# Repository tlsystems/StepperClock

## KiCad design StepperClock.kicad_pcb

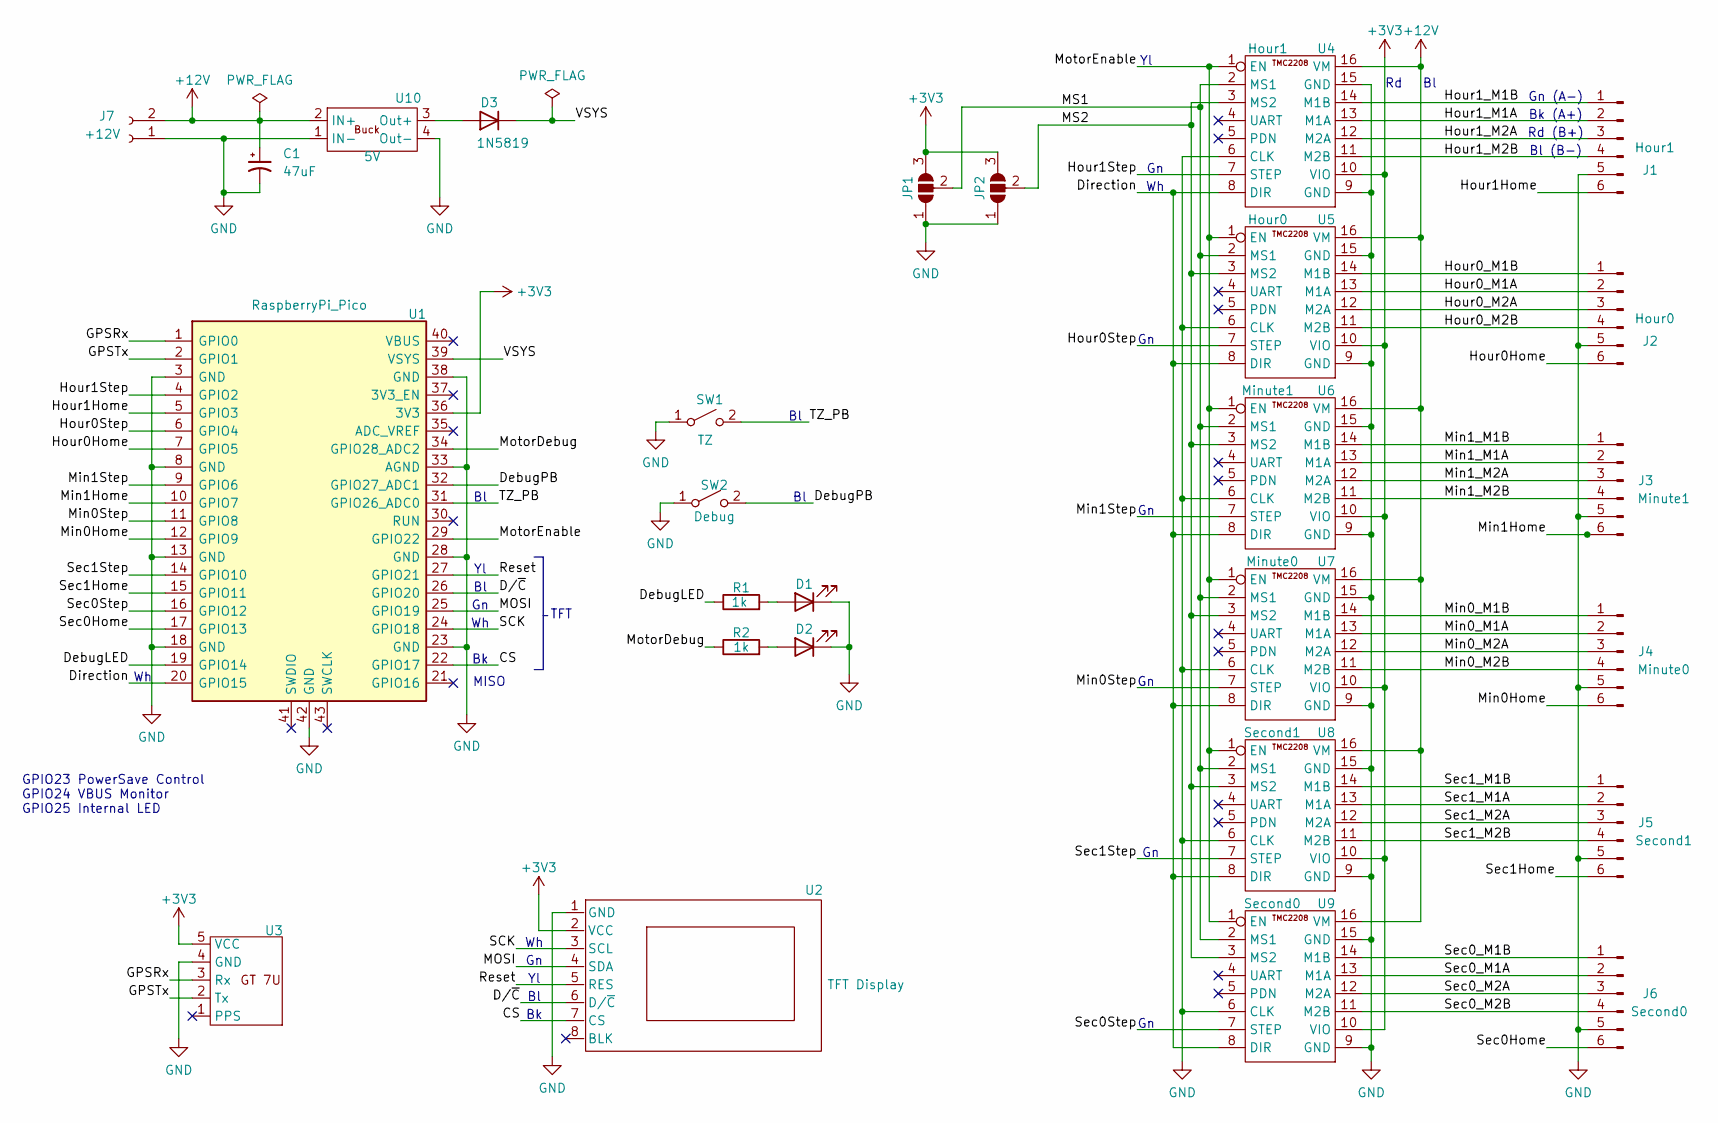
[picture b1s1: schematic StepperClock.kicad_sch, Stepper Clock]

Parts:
C1: 47uF; CP_Radial_D8.0mm_P2.50mm
D1, D2: LED; D_0805_2012Metric_Pad1.15x1.40mm_HandSolder
D3: 1N5819; D_DO-41_SOD81_P7.62mm_Horizontal
J1: Hour1; JST_PH_B6B-PH-K_1x06_P2.00mm_Vertical
J2: Hour0; JST_PH_B6B-PH-K_1x06_P2.00mm_Vertical
J3: Minute1; JST_PH_B6B-PH-K_1x06_P2.00mm_Vertical
J4: Minute0; JST_PH_B6B-PH-K_1x06_P2.00mm_Vertical
J5: Second1; JST_PH_B6B-PH-K_1x06_P2.00mm_Vertical
J6: Second0; JST_PH_B6B-PH-K_1x06_P2.00mm_Vertical
J7: +12V; PinHeader_1x02_P2.54mm_Vertical
JP1, JP2: SolderJumper-3_P2.0mm_Open_TrianglePad1.0x1.5mm
R1, R2: 1k; R_0805_2012Metric_Pad1.20x1.40mm_HandSolder
SW1: TZ; SW_PUSH-12mm
SW2: Debug; SW_PUSH-12mm
U1: RaspberryPi_Pico; RaspberryPi_Pico_Common_THT
U2: TFT Display; TFT_Display_.94in
U3: GT-U7 GPS
U4: Hour1; TMC2208_Breakout
U5: Hour0; TMC2208_Breakout
U6: Minute1; TMC2208_Breakout
U7: Minute0; TMC2208_Breakout
U8: Second1; TMC2208_Breakout
U9: Second0; TMC2208_Breakout
U10: 5V; 5V Buck Converter

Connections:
+3V3: JP1.3 (B), JP2.3 (B), U1.36 (3V3), U2.2 (VCC), U3.5 (VCC), U4.10 (VIO), U5.10 (VIO), U6.10 (VIO), U7.10 (VIO), U8.10 (VIO), U9.10 (VIO)
+12V: C1.1, J7.2, U4.16 (VM), U5.16 (VM), U6.16 (VM), U7.16 (VM), U8.16 (VM), U9.16 (VM), U10.2 (IN+)
/CS: U1.22 (GPIO17), U2.7 (CS)
/DebugLED: R1.1, U1.19 (GPIO14)
/DebugPB: SW2.2 (B), U1.32 (GPIO27_ADC1)
/Direction: U1.20 (GPIO15), U4.8 (DIR), U5.8 (DIR), U6.8 (DIR), U7.8 (DIR), U8.8 (DIR), U9.8 (DIR)
/D/~C: U1.26 (GPIO20), U2.6 (D/~C)
/GPSRx: U1.1 (GPIO0), U3.3 (Rx)
/GPSTx: U1.2 (GPIO1), U3.2 (Tx)
/Hour0Home: J2.6, U1.7 (GPIO5)
/Hour0Step: U1.6 (GPIO4), U5.7 (STEP)
/Hour0_M1A: J2.2, U5.13 (M1A)
/Hour0_M1B: J2.1, U5.14 (M1B)
/Hour0_M2A: J2.3, U5.12 (M2A)
/Hour0_M2B: J2.4, U5.11 (M2B)
/Hour1Home: J1.6, U1.5 (GPIO3)
/Hour1Step: U1.4 (GPIO2), U4.7 (STEP)
/Hour1_M1A: J1.2, U4.13 (M1A)
/Hour1_M1B: J1.1, U4.14 (M1B)
/Hour1_M2A: J1.3, U4.12 (M2A)
/Hour1_M2B: J1.4, U4.11 (M2B)
/MOSI: U1.25 (GPIO19), U2.4 (SDA)
/MS1: JP1.2 (C), U4.2 (MS1), U5.2 (MS1), U6.2 (MS1), U7.2 (MS1), U8.2 (MS1), U9.2 (MS1)
/MS2: JP2.2 (C), U4.3 (MS2), U5.3 (MS2), U6.3 (MS2), U7.3 (MS2), U8.3 (MS2), U9.3 (MS2)
/Min0Home: J4.6, U1.12 (GPIO9)
/Min0Step: U1.11 (GPIO8), U7.7 (STEP)
/Min0_M1A: J4.2, U7.13 (M1A)
/Min0_M1B: J4.1, U7.14 (M1B)
/Min0_M2A: J4.3, U7.12 (M2A)
/Min0_M2B: J4.4, U7.11 (M2B)
/Min1Home: J3.6, U1.10 (GPIO7)
/Min1Step: U1.9 (GPIO6), U6.7 (STEP)
/Min1_M1A: J3.2, U6.13 (M1A)
/Min1_M1B: J3.1, U6.14 (M1B)
/Min1_M2A: J3.3, U6.12 (M2A)
/Min1_M2B: J3.4, U6.11 (M2B)
/MotorDebug: R2.1, U1.34 (GPIO28_ADC2)
/MotorEnable: U1.29 (GPIO22), U4.1 (EN), U5.1 (EN), U6.1 (EN), U7.1 (EN), U8.1 (EN), U9.1 (EN)
/Reset: U1.27 (GPIO21), U2.5 (RES)
/SCK: U1.24 (GPIO18), U2.3 (SCL)
/Sec0Home: J6.6, U1.17 (GPIO13)
/Sec0Step: U1.16 (GPIO12), U9.7 (STEP)
/Sec0_M1A: J6.2, U9.13 (M1A)
/Sec0_M1B: J6.1, U9.14 (M1B)
/Sec0_M2A: J6.3, U9.12 (M2A)
/Sec0_M2B: J6.4, U9.11 (M2B)
/Sec1Home: J5.6, U1.15 (GPIO11)
/Sec1Step: U1.14 (GPIO10), U8.7 (STEP)
/Sec1_M1A: J5.2, U8.13 (M1A)
/Sec1_M1B: J5.1, U8.14 (M1B)
/Sec1_M2A: J5.3, U8.12 (M2A)
/Sec1_M2B: J5.4, U8.11 (M2B)
/TZ_PB: SW1.2 (B), U1.31 (GPIO26_ADC0)
/VSYS: D3.1 (K), U1.39 (VSYS)
GND: C1.2, D1.1 (K), D2.1 (K), J1.5, J2.5, J3.5, J4.5, J5.5, J6.5, J7.1, JP1.1 (A), JP2.1 (A), SW1.1 (A), SW2.1 (A), U1.3 (GND), U1.8 (GND), U1.13 (GND), U1.18 (GND), U1.23 (GND), U1.28 (GND), U1.33 (AGND), U1.38 (GND), U1.42 (GND), U2.1 (GND), U3.4 (GND), U4.6 (CLK), U4.9 (GND), U4.15 (GND), U5.6 (CLK), U5.9 (GND), U5.15 (GND), U6.6 (CLK), U6.9 (GND), U6.15 (GND), U7.6 (CLK), U7.9 (GND), U7.15 (GND), U8.6 (CLK), U8.9 (GND), U8.15 (GND), U9.6 (CLK), U9.9 (GND), U9.15 (GND), U10.1 (IN-), U10.4 (Out-)
unnamed: D1.2 (A), R1.2
unnamed: D2.2 (A), R2.2
unnamed: D3.2 (A), U10.3 (Out+)

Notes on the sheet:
MISO
Gn (A-)
Rd (B+)
TFT
GPIO23 PowerSave Control GPIO24 VBUS Monitor GPIO25 Internal LED
Bk (A+)
Bl (B-)

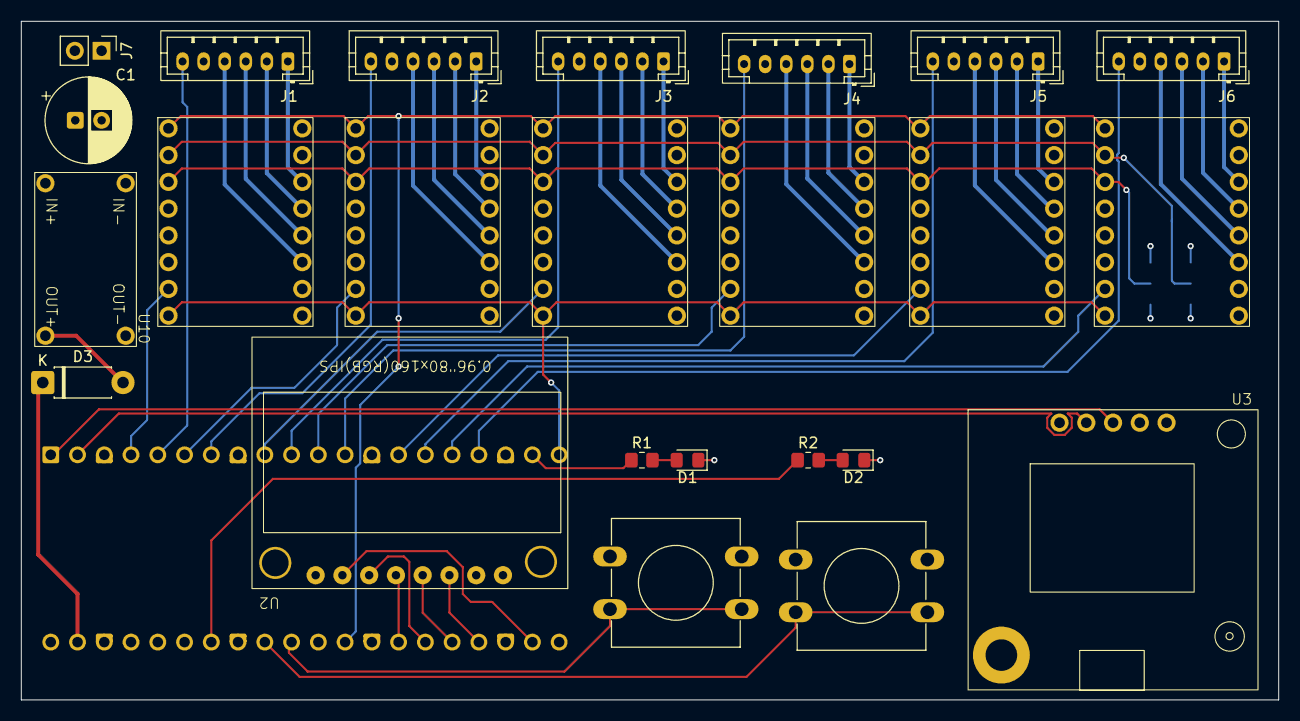
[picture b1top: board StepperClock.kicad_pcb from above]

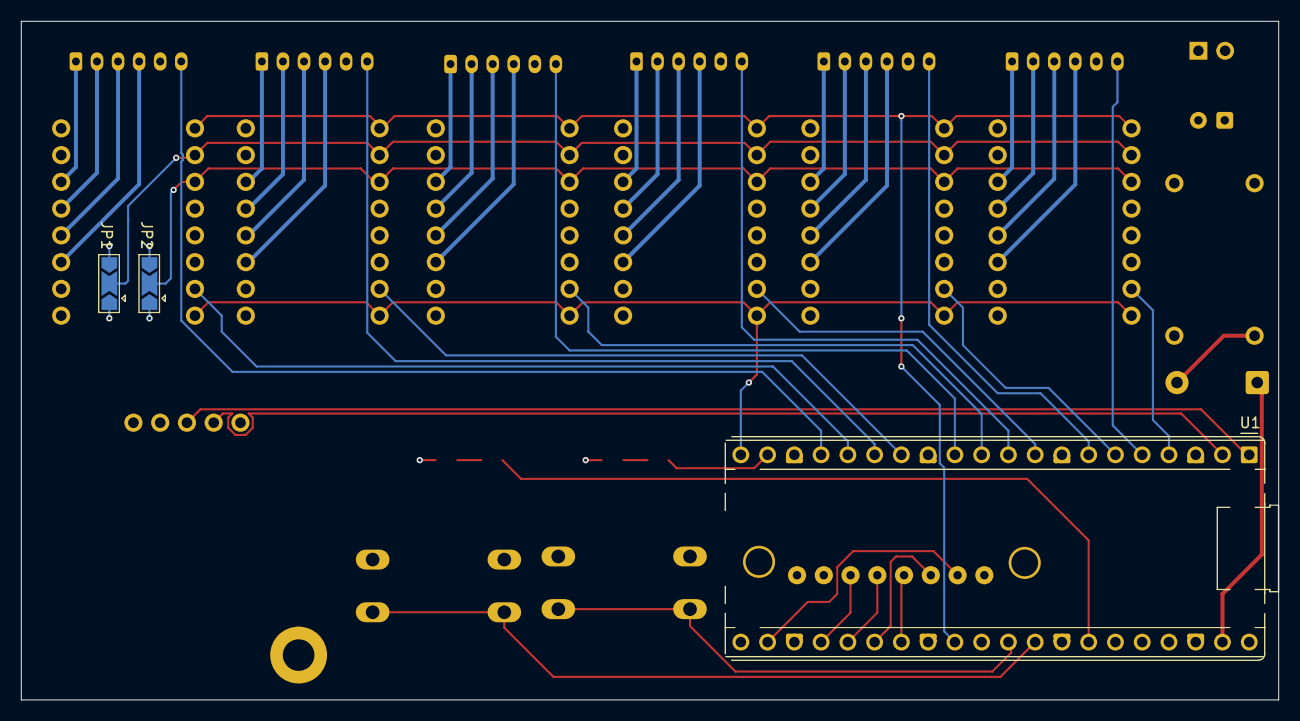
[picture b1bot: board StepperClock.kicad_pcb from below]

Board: 4 copper layers, 119.4 x 64.4 mm, 27 parts (3 on the bottom side), 58 nets.

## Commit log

2026-03-03 Initial commit to Git
2026-03-03 Added debug LED and pushbutton
2026-03-04 Remove backup directory from repository Finish board routing
2026-03-04 Add .gitignore and 1N5819 diode data sheet
